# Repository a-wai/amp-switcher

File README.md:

# Amp Switcher

Table of contents:
* [Relays Array](#relays-array)
* [Control Matrix](#control-matrix)
* [Building](#building)
* [Licensing](#licensing)

---

The Amp Switcher is a device for easily switching between (guitar) amplifiers
when a single speaker cabinet is used and/or available.

It is designed so that, at any given moment:
* the guitar input is routed to the selected amp (and only this one!)
* the selected amp's output (and only this one!) is routed to the cab
* all unused amps have their input muted ("shorted" in electrical terms)
* all unused amps have a dummy (resistive) load connected to their speaker
  output

Note: this repository only includes the electronics schematics and PCB designs.
Mechanical design and building is left to the reader's skills and imagination.

## Relays Array

This is the part responsible for the actual switching. In order to minimize the
number of different parts needed, this PCB is meant to be "universal", in the
sense that it can be used both for the "Guitar -> Amp Inputs" section (with an
optional built-in buffer) and for the "Amp Outputs -> Speaker Cab" one.

The board should be populated differently depending on the intended function:
* for a speaker out board, the 2W resistors (R1-R8) should be populated,
  especially when used with tube amplifiers
* guitar in boards shouldn't include those resistors, but instead the
  corresponding solder jumpers should be bridged by applying solder across them

The input/output section (part of the PCB on the left of J1 & K1) can also be
used in 4 different ways:
* external connector, direct routing: do not populate any component except J10
  (+12V) and **J15** (to/from external connector)
* on-board jack connector, direct routing (recommended for speaker out board):
  populate only J14 and J10, and (generously) apply solder across JPX1
* external connector, input buffer (only suitable for "guitar input" board): do
  not populate any component except J10 (+12V) and **J16** (to/from external
  connector)
* on-board jack connector, input buffer (only suitable for "guitar input"
  board): populate all components except J15 and J16

Finally, the PCB is split in blocks of 2 relays, with oblong holes in the board
so it can easily be broken to only keep the needed number of I/Os. This allows
the same design to be used in projects of different sizes. Of course, you can
avoid wasting material by using the properly-sized PCB: we provide design and
Gerber files for variants with 2, 4, 6 or 8 relays.

**WARNING: although using relatively wide (2mm) PCB tracks, we recommend the
boards to be manufactured with 2oz copper weight if they are to be used with
amplifiers above 20W RMS of nominal output power.**

## Control Matrix

The control board is kept as simple as possible: it is made of a single rotary
switch, with as many LEDs as needed to indicate the currently selected amp. The
first switch position (fully counter-clockwise) is the OFF position where no
amplifier is selected; turning the switch clockwise will select amplifiers one
after another, lighting the corresponding LED on (the first being D1 -- the
leftmost one -- then D2, D3 and so on...).

This PCB is meant to be mounted directly on the front panel, with screw
terminals on the opposite side of the board for connecting to the corresponding
terminals of the "Relays Array" boards. Like the latter, it also includes
oblong holes for easily resizing the PCB to your needs (watch out for
[#1](https://github.com/a-wai/amp-switcher/issues/1) though), and we still
provide design and Gerber files for 2/4/6/8-way variants.

Finally, a simpler (and more compact) version is also provided for 2-way
devices, using a smaller ON-OFF-ON toggle switch instead of the rotary one.

*Note: those familiar with matrices will likely notice the "Control Matrix"
naming isn't really accurate, as a 1xN matrix is basically an array, just like
the "Relays Array" board is; however I didn't want to use "array" in both
boards' names, and I think it sounds better that way anyway* 😉

## Building

This project was kindly sponsored by [PCBWay](https://www.pcbway.com) who
provided PCBs for the prototype builds free of charge, many thanks to them!
Moreover, working with this company has been a really nice experience:
* the ordering process was as easy as it gets (upload Gerber files, select
  features, place order, and that's it!)
* build time was 3-4 days as announced at order time (they also offer "express"
  options for an additional fee)
* quality and finish are both excellent! 👍

When populating the boards, one should place and solder the components in the
following order:

1. Jumpers as needed (R1-R8 on the input board, JPX1 on the output one -- and
   on the input board **when not wiring the optional buffer**)
1. Diodes & low-wattage resistors
1. *Input board w/ buffer only:* DIP-8 socket & 100 nF capacitors
1. Screw terminals
1. *Input board w/ buffer only:* electrolytic capacitors
1. Relays & jack connectors
1. *Output board only:* 2W resistors; keeping the resistors' bodies away from
   the board is a good idea in case things go wrong: only the resistor will
   burn, not the PCB!

For the control matrix board, resistors should be mounted first, then the
rotary switch. The LEDs are first mounted on the front panel, then soldered
after putting the board in place (this can be tricky, but is feasible).

A few additional notes:

* R1-R8 values should be tweaked depending on the LEDs used, especially when
  using various colors (e.g. 10k could work fine for blue LEDs, 5.1k for orange
  ones, and 47k for "warm white" LEDs)
* the GND post of the output board should remain unconnected
* on this same board, the jumper connecting the ground plane to the GND signal
  should be cut (this will probably be converted to an open solder jumper soon)

Once all the boards are in place (but not fully secured yet), one just has to
run the wires to/from the appropriate solder terminals and the DC input
connector. Here, using wires of various different colors is an efficient way
not to get lost and ensure the wiring is correct.

## Licensing

Copyright 2025 Arnaud Ferraris.

3D models for the Neutrik jacks are © Inventor eFX Technology and have been
downloaded from https://www.inventfx.com/_ifxkicad/_ifxkicadxtra.htm

3D models for the rotary and toggle switches aren't included due to licensing
restrictions, but they can be downloaded from https://componentsearchengine.com
* [CK1049](https://componentsearchengine.com/part-view/CK1049/Lorlin) rotary
  switch
* [A105SYZQ04](https://componentsearchengine.com/part-view/A105SYZQ04/TE%20Connectivity)
  toggle switch

This source describes Open Hardware and is licensed under the CERN-OHL-S v2.

You may redistribute and modify this source and make products using it
under the terms of the CERN-OHL-S v2 (https://ohwr.org/cern_ohl_s_v2.txt).

This source is distributed WITHOUT ANY EXPRESS OR IMPLIED WARRANTY, INCLUDING
OF MERCHANTABILITY, SATISFACTORY QUALITY AND FITNESS FOR A PARTICULAR PURPOSE.
Please see the CERN-OHL-S v2 for applicable conditions.

Source location: https://github.com/a-wai/amp-switcher

As per CERN-OHL-S v2 section 4, should You produce hardware based on this
source, You must where practicable maintain the Source Location visible on the
PCBs and user documentation of the Amp Switcher or other products you make
using this source.

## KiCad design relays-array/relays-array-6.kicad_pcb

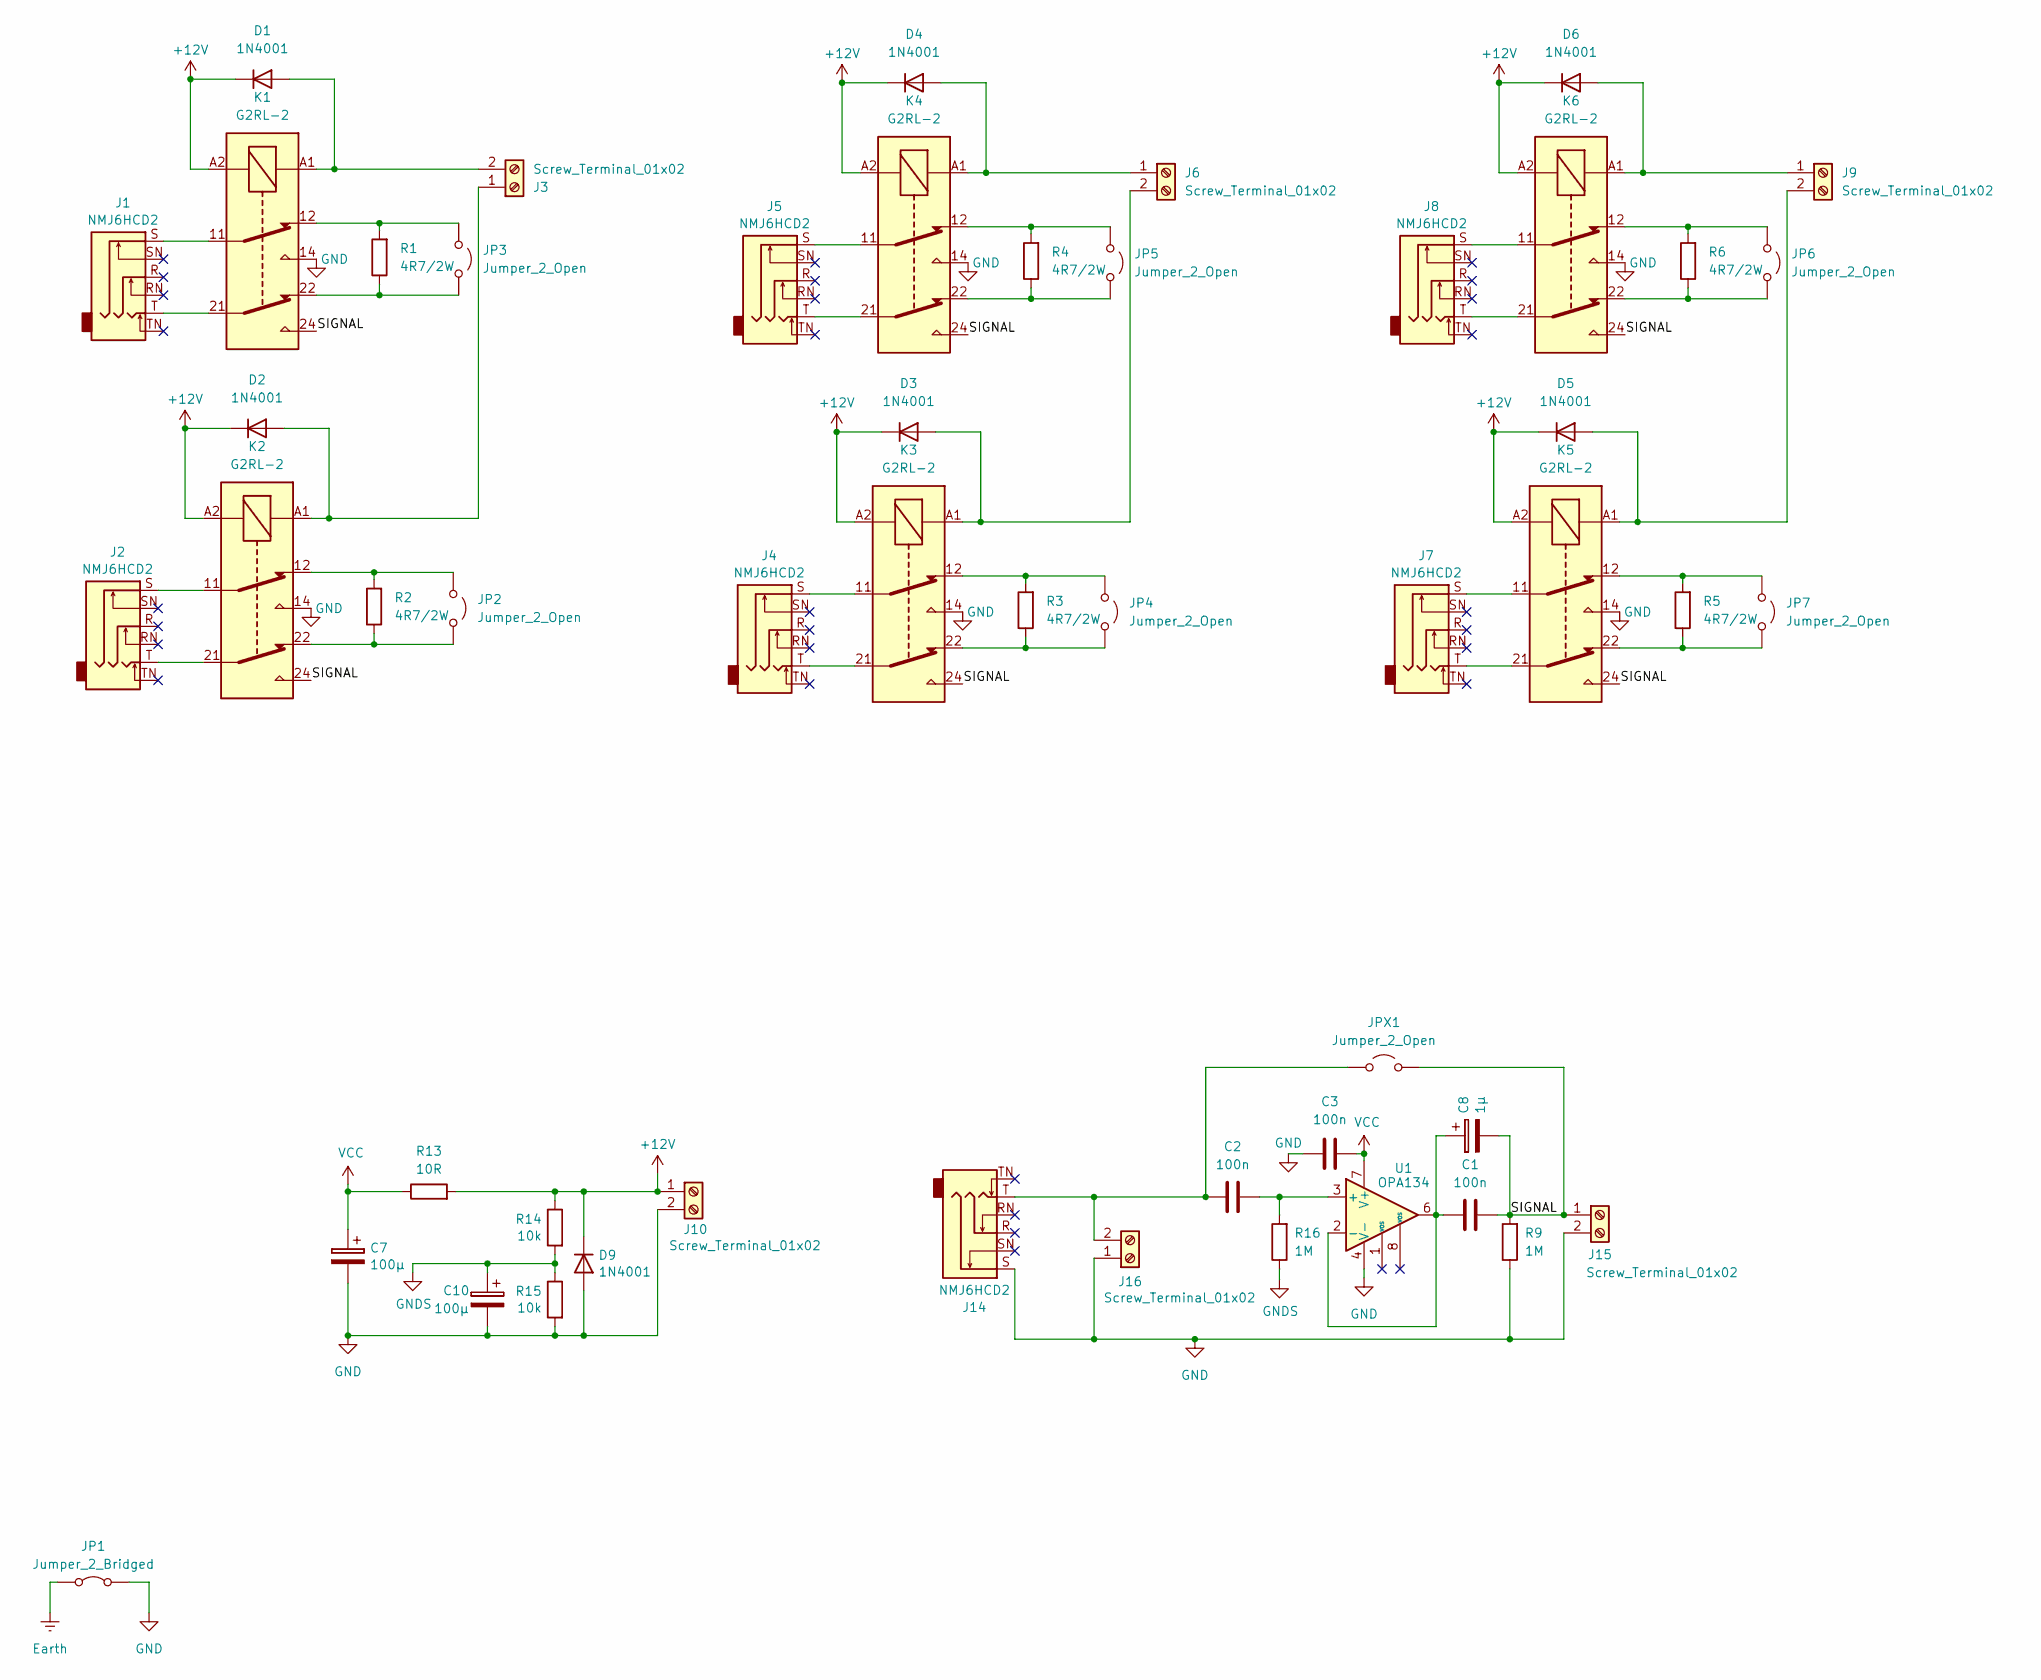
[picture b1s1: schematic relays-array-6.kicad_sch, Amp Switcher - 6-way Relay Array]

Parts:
C1, C2, C3: 100n; C_Rect_L7.2mm_W3.5mm_P5.00mm_FKS2_FKP2_MKS2_MKP2
C7: 100µ; CP_Radial_D5.0mm_P2.00mm
C8: 1µ; CP_Radial_D5.0mm_P2.00mm
C10: 100µ; CP_Radial_D5.0mm_P2.00mm; MPN FW
D1, D2, D3, D4, D5, D6, D9: 1N4001; D_DO-41_SOD81_P7.62mm_Horizontal
J1, J2, J4, J5, J7, J8, J14: NMJ6HCD2; Jack_6.35mm_Neutrik_NMJ6HCD2_Horizontal
J3, J6, J9, J10, J15, J16: Screw_Terminal_01x02; TerminalBlock_bornier-2_P5.08mm
JP1: Jumper_2_Bridged; SolderJumper-2_P1.3mm_Bridged_RoundedPad1.0x1.5mm
JP2, JP3, JP4, JP5, JP6, JP7: Jumper_2_Open; SolderJumper-2_P1.3mm_Open_RoundedPad1.0x1.5mm
JPX1: Jumper_2_Open; SolderJumper-2_P1.3mm_Open_Pad1.0x1.5mm
K1, K2, K3, K4, K5, K6: G2RL-2; Relay_DPDT_Omron_G2RL-2
R1, R2, R3, R4, R5, R6: 4R7/2W; R_Axial_DIN0414_L11.9mm_D4.5mm_P15.24mm_Horizontal
R9, R16: 1M; R_Axial_DIN0207_L6.3mm_D2.5mm_P7.62mm_Horizontal
R13: 10R; R_Axial_DIN0207_L6.3mm_D2.5mm_P7.62mm_Horizontal
R14, R15: 10k; R_Axial_DIN0207_L6.3mm_D2.5mm_P7.62mm_Horizontal
U1: OPA134; DIP-8_W7.62mm_Socket_LongPads

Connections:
+12V: D1.1 (K), D2.1 (K), D3.1 (K), D4.1 (K), D5.1 (K), D6.1 (K), D9.1 (K), J10.1, K1.A2, K2.A2, K3.A2, K4.A2, K5.A2, K6.A2, R13.2, R14.1
/SIGNAL: C1.1, C8.2, J15.1, JPX1.1 (A), K1.24, K2.24, K3.24, K4.24, K5.24, K6.24, R9.2
Earth: JP1.1 (A)
GND: C3.2, C7.2, C10.2, D9.2 (A), J10.2, J14.S, J15.2, J16.1, JP1.2 (B), K1.14, K2.14, K3.14, K4.14, K5.14, K6.14, R9.1, R15.2, U1.4 (V-)
GNDS: C10.1, R14.2, R15.1, R16.1
unnamed: D1.2 (A), J3.2, K1.A1
unnamed: D2.2 (A), J3.1, K2.A1
unnamed: D3.2 (A), J6.2, K3.A1
unnamed: D4.2 (A), J6.1, K4.A1
unnamed: D5.2 (A), J9.2, K5.A1
unnamed: D6.2 (A), J9.1, K6.A1
unnamed: J1.S, K1.11
unnamed: J1.T, K1.21
unnamed: J2.S, K2.11
unnamed: J2.T, K2.21
unnamed: J4.S, K3.11
unnamed: J4.T, K3.21
unnamed: J5.S, K4.11
unnamed: J5.T, K4.21
unnamed: J7.S, K5.11
unnamed: J7.T, K5.21
unnamed: J8.S, K6.11
unnamed: J8.T, K6.21
unnamed: C2.2, J14.T, J16.2, JPX1.2 (B)
unnamed: JP2.1 (A), K2.12, R2.2
unnamed: JP2.2 (B), K2.22, R2.1
unnamed: JP3.1 (A), K1.12, R1.2
unnamed: JP3.2 (B), K1.22, R1.1
unnamed: JP4.1 (A), K3.12, R3.2
unnamed: JP4.2 (B), K3.22, R3.1
unnamed: JP5.1 (A), K4.12, R4.2
unnamed: JP5.2 (B), K4.22, R4.1
unnamed: JP6.1 (A), K6.12, R6.2
unnamed: JP6.2 (B), K6.22, R6.1
unnamed: JP7.1 (A), K5.12, R5.2
unnamed: JP7.2 (B), K5.22, R5.1
unnamed: C2.1, R16.2, U1.3 (+)
unnamed: C1.2, C8.1, U1.2 (-), U1.6
VCC: C3.1, C7.1, R13.1, U1.7 (V+)

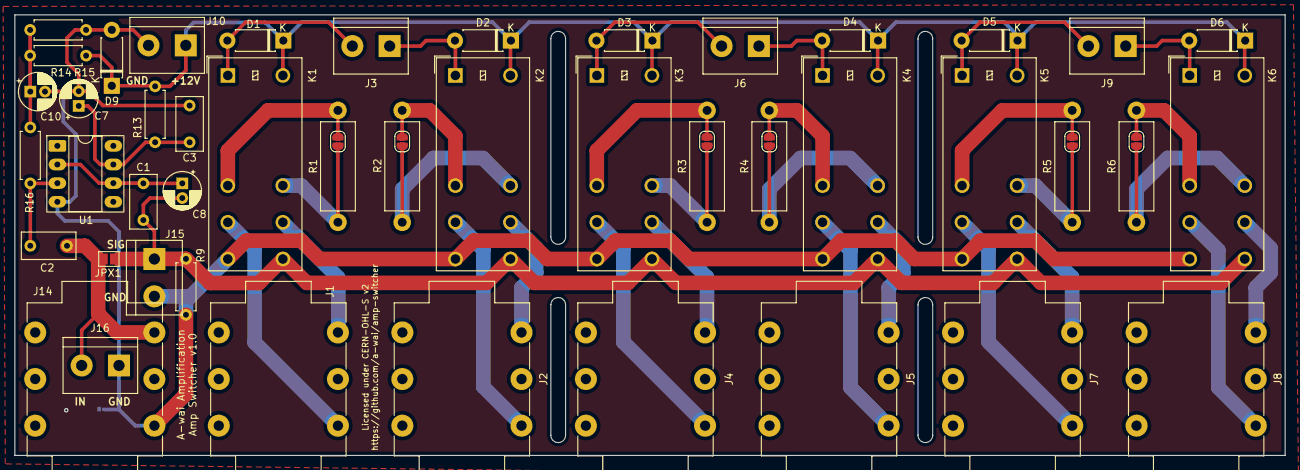
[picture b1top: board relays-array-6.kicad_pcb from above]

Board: 2 copper layers, 173.0 x 60.0 mm, 52 parts (1 on the bottom side), 38 nets.

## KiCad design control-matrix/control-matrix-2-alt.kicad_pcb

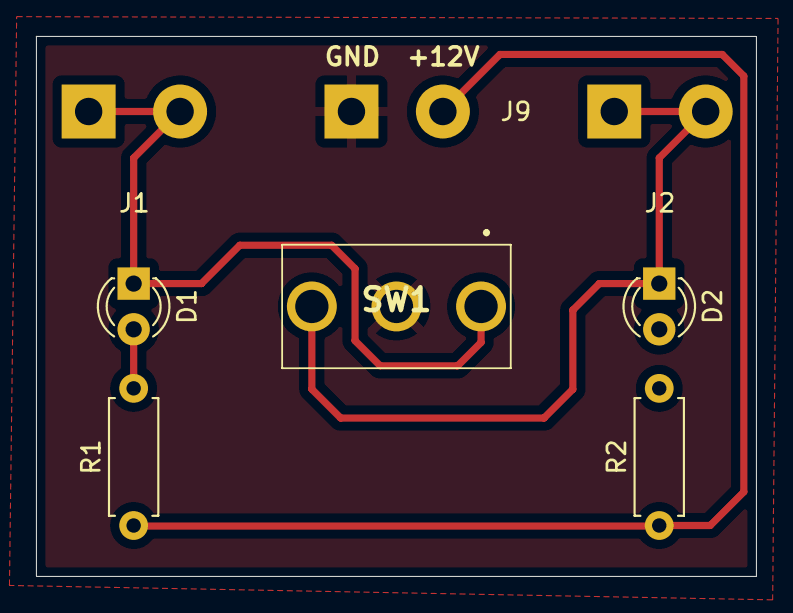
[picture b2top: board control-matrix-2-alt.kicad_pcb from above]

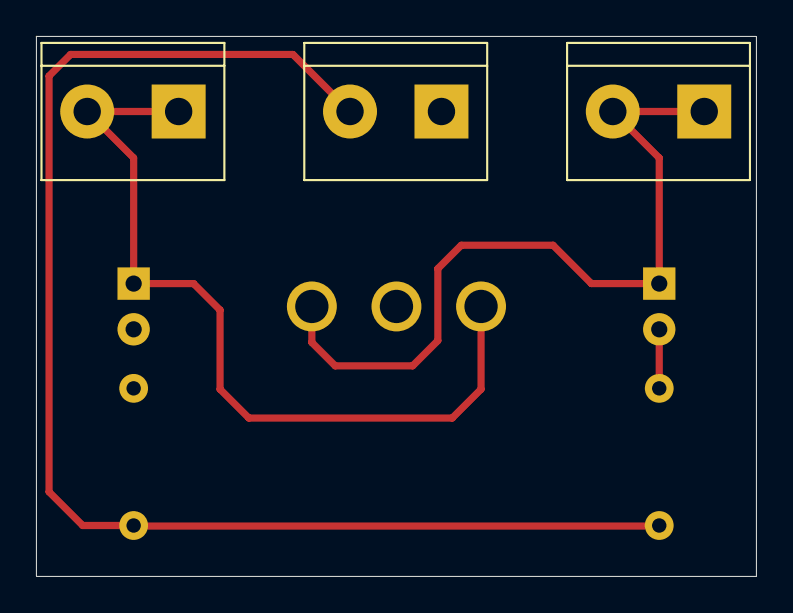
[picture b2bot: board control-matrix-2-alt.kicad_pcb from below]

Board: 2 copper layers, 40.0 x 30.0 mm, 8 parts (3 on the bottom side), 6 nets.

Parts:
D1, D2: LED; LED_D3.0mm
J1, J2, J9: Screw_Terminal_01x02; TerminalBlock_bornier-2_P5.08mm
R1, R2: 680R; R_Axial_DIN0207_L6.3mm_D2.5mm_P7.62mm_Horizontal
SW1: SW_SPDT; SPDT_Toggle

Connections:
+12V: J9.2, R1.1, R2.1
GND: J9.1, SW1.2 (B)
unnamed: D1.2 (A), R1.2
unnamed: D1.1 (K), J1.1, J1.2, SW1.1 (A)
unnamed: D2.2 (A), R2.2
unnamed: D2.1 (K), J2.1, J2.2, SW1.3 (C)

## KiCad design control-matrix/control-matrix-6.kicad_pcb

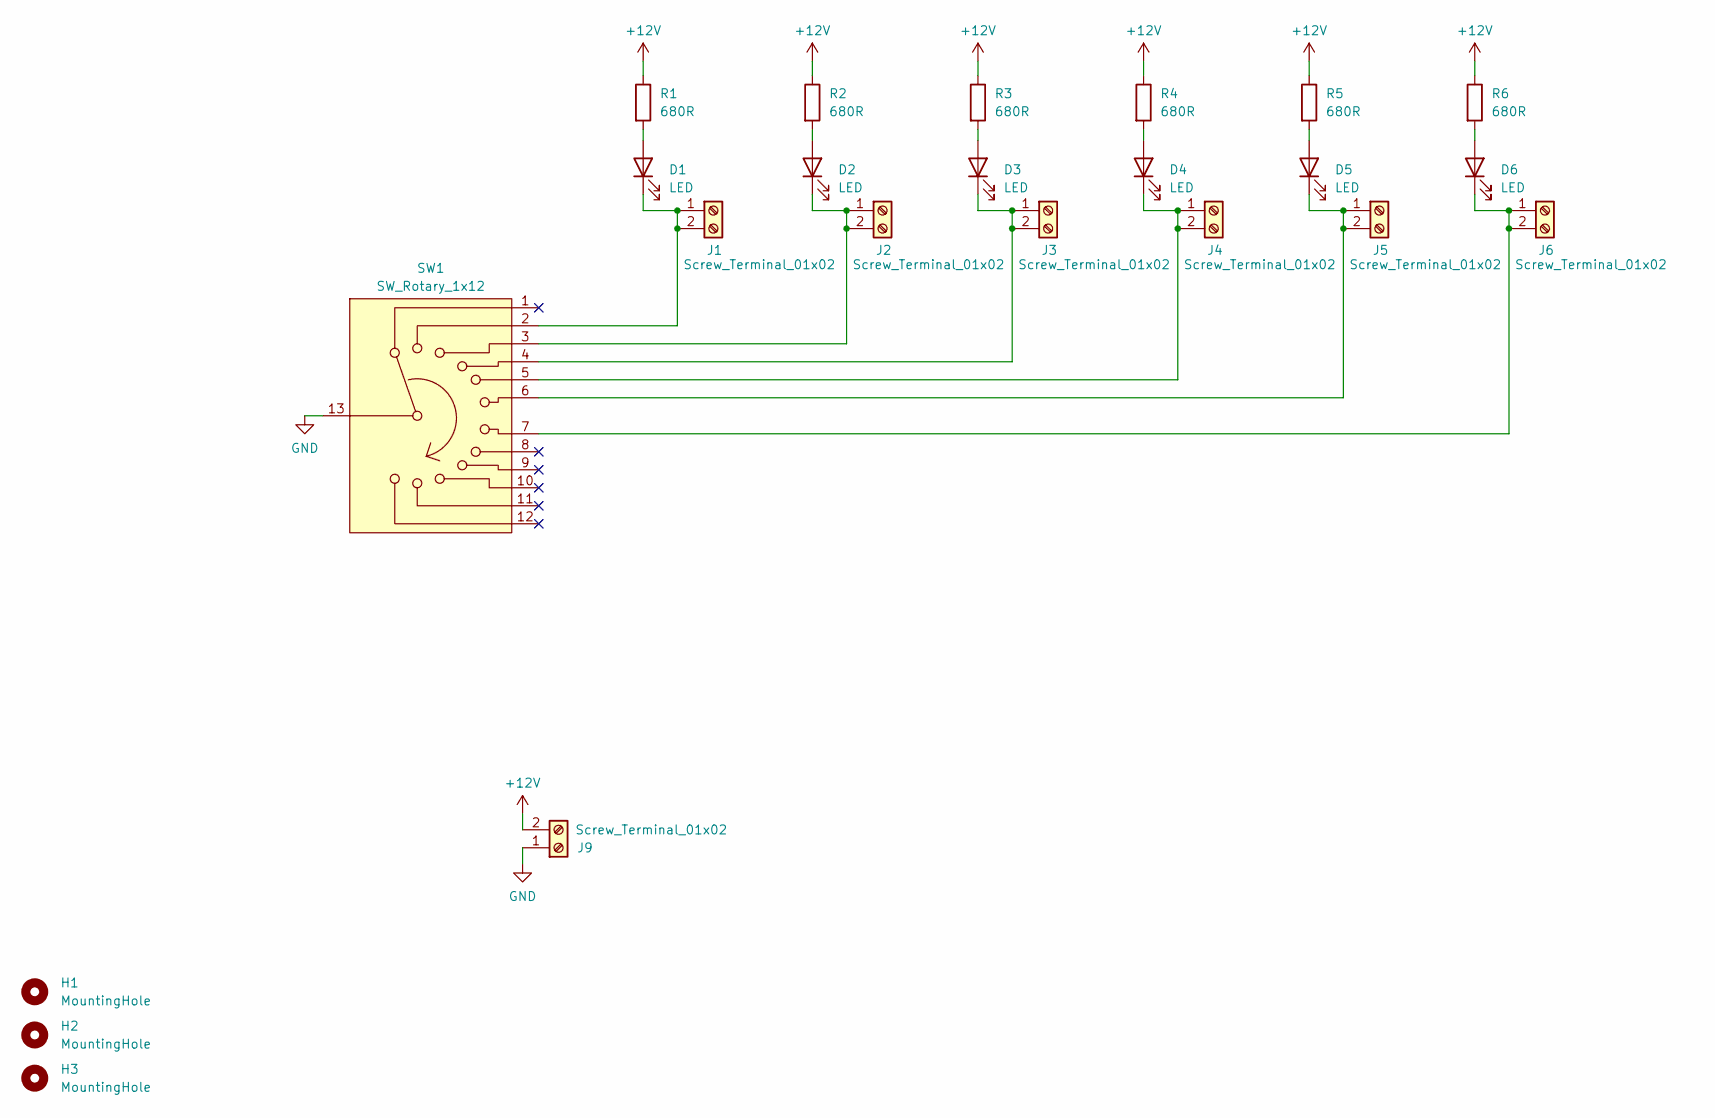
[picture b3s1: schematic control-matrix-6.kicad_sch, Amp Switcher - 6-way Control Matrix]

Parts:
D1, D2, D3, D4, D5, D6: LED; LED_D3.0mm
H1, H2, H3: MountingHole; MountingHole_3.2mm_M3
J1, J2, J3, J4, J5, J6, J9: Screw_Terminal_01x02; TerminalBlock_bornier-2_P5.08mm
R1, R2, R3, R4, R5, R6: 680R; R_Axial_DIN0207_L6.3mm_D2.5mm_P7.62mm_Horizontal
SW1: SW_Rotary_1x12; CK1059

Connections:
+12V: J9.2, R1.1, R2.1, R3.1, R4.1, R5.1, R6.1
GND: J9.1, SW1.13
unnamed: D1.2 (A), R1.2
unnamed: D1.1 (K), J1.1, J1.2, SW1.2
unnamed: D2.2 (A), R2.2
unnamed: D2.1 (K), J2.1, J2.2, SW1.3
unnamed: D3.2 (A), R3.2
unnamed: D3.1 (K), J3.1, J3.2, SW1.4
unnamed: D4.2 (A), R4.2
unnamed: D4.1 (K), J4.1, J4.2, SW1.5
unnamed: D5.2 (A), R5.2
unnamed: D5.1 (K), J5.1, J5.2, SW1.6
unnamed: D6.2 (A), R6.2
unnamed: D6.1 (K), J6.1, J6.2, SW1.7

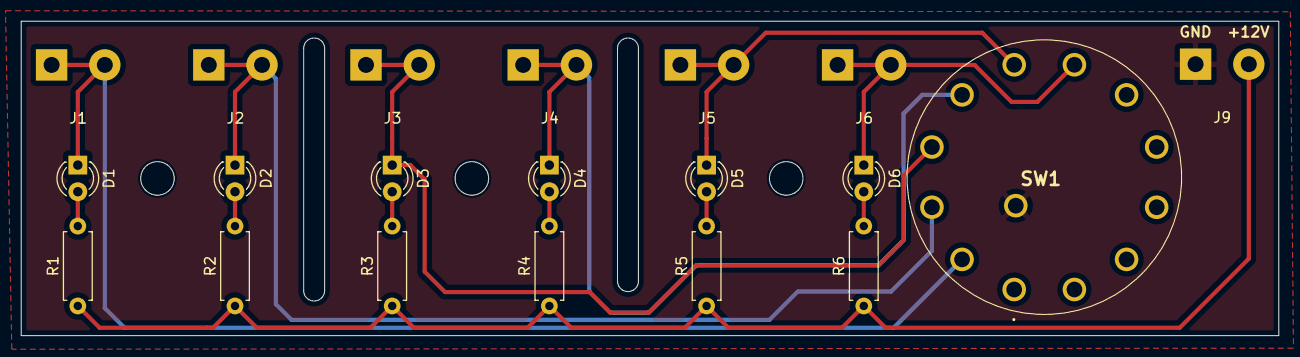
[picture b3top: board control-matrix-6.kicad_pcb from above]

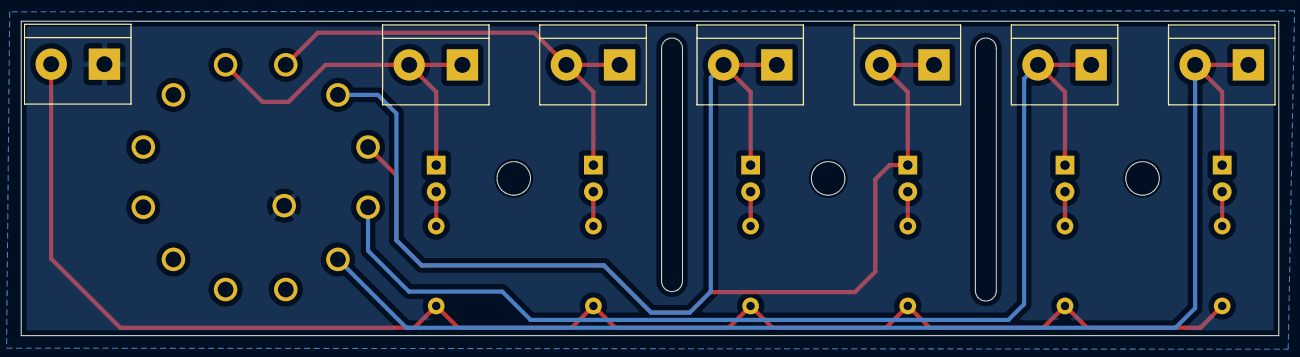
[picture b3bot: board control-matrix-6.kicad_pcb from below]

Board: 2 copper layers, 120.0 x 30.0 mm, 23 parts (7 on the bottom side), 14 nets.

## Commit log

2025-03-12 relays-array: add actual DIP-8 device on socket
2025-03-12 relays-array: add 2/4/6-relays variants
2025-03-12 relays-array: add terminal block for buffer use w/ external connector
2025-03-17 Add control-matrix boards for 2/4/6/8-way devices
2025-03-17 control-matrix: add smaller alternate version for 2-way devices
2025-03-17 control-matrix: add power input labels on silkscreen
2025-03-17 relays-array: add terminal block labels on silkscreen
2025-03-18 control-matrix: 2-alt: move switch to center of board
2025-03-20 control-matrix: add ground planes
    This avoids having to etch too much copper.
2025-03-20 relays-array: fix schematics error and add ground plane
    The jack connectors are all (except for the buffer input) wired
    backwards, with the tip going to `GND` and the sleeve on `SIGNAL`, while
    it should be the other way around.
    While at it, improve a bit the PCB tracks and add a ground plane. The
    latter is only connected to `GND` in a single point in order to avoid
    ground loops and other unpleasant issues.
2025-04-07 README: add paragraph about building
2025-04-07 README: add reference to the control board resizing issue
2025-04-07 README: add ToC

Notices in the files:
control-matrix/control-matrix-2-alt.kicad_pcb:
SPDX-FileCopyrightText: 2025 Arnaud Ferraris
SPDX-License-Identifier: CERN-OHL-S-2.0+
relays-array/relays-array-6.kicad_pcb:
Licensed under CERN-OHL-S v2
